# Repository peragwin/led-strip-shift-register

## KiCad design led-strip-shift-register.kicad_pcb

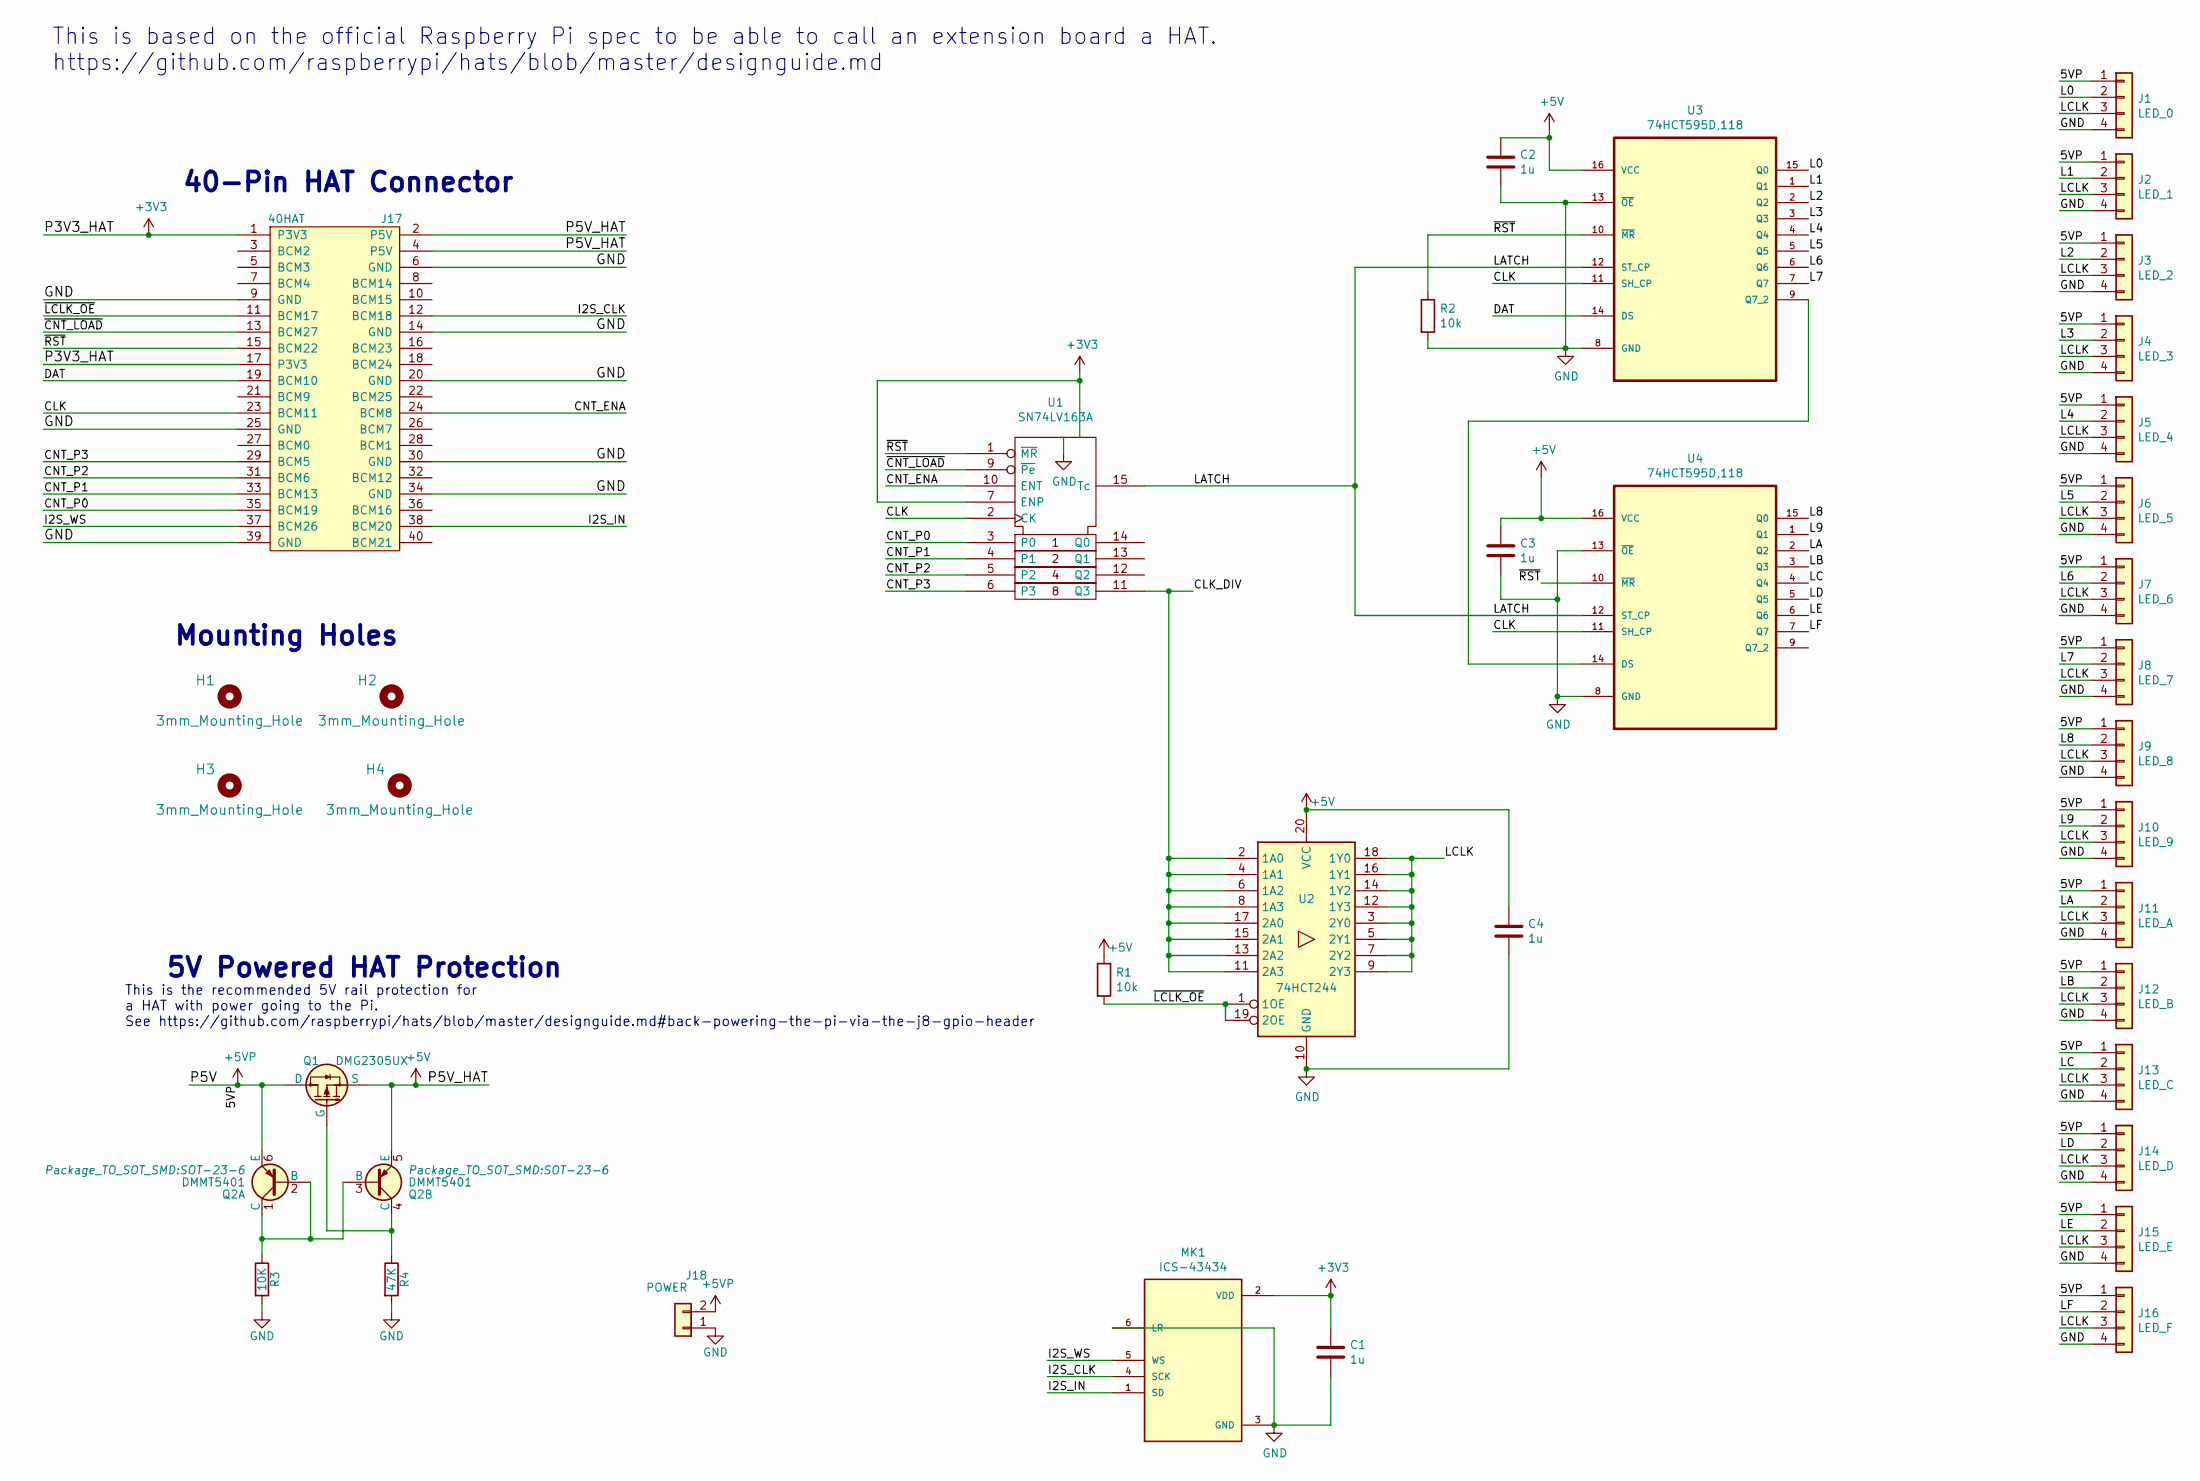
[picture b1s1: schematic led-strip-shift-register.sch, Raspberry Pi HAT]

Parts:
C1, C2, C3, C4: 1u; C_0603_1608Metric_Pad1.08x0.95mm_HandSolder
H1, H2, H3, H4: 3mm_Mounting_Hole; NPTH_3mm_ID
J1: LED_0; PinSocket_1x04_P2.54mm_Vertical
J2: LED_1; PinSocket_1x04_P2.54mm_Vertical
J3: LED_2; PinSocket_1x04_P2.54mm_Vertical
J4: LED_3; PinSocket_1x04_P2.54mm_Vertical
J5: LED_4; PinSocket_1x04_P2.54mm_Vertical
J6: LED_5; PinSocket_1x04_P2.54mm_Vertical
J7: LED_6; PinSocket_1x04_P2.54mm_Vertical
J8: LED_7; PinSocket_1x04_P2.54mm_Vertical
J9: LED_8; PinSocket_1x04_P2.54mm_Vertical
J10: LED_9; PinSocket_1x04_P2.54mm_Vertical
J11: LED_A; PinSocket_1x04_P2.54mm_Vertical
J12: LED_B; PinSocket_1x04_P2.54mm_Vertical
J13: LED_C; PinSocket_1x04_P2.54mm_Vertical
J14: LED_D; PinSocket_1x04_P2.54mm_Vertical
J15: LED_E; PinSocket_1x04_P2.54mm_Vertical
J16: LED_F; PinSocket_1x04_P2.54mm_Vertical
J17: 40HAT; PinSocket_2x20_P2.54mm_Vertical
J18: POWER; TerminalBlock_bornier-2_P5.08mm
MK1: ICS-43434; I2S-MIC_DIP-6
Q1: DMG2305UX; SOT-23
Q2: DMMT5401; SOT-23-6
R1, R2: 10k; R_0603_1608Metric_Pad0.98x0.95mm_HandSolder
R3: 10K; R_0603_1608Metric_Pad0.84x1.00mm_HandSolder
R4: 47K; R_0603_1608Metric_Pad0.84x1.00mm_HandSolder
U1: SN74LV163A; SOIC-16_3.9x9.9mm_P1.27mm
U2: 74HCT244; TSSOP-20_4.4x6.5mm_P0.65mm; LCSC C131088
U3, U4: 74HCT595D,118; SOIC127P600X175-16N; MPN 74HCT595D,118; LCSC C282339

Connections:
+3V3: C1.1, J17.1 (P3V3), J17.17 (P3V3), MK1.2 (VDD), U1.7 (ENP), U1.16 (VCC)
+5V: C2.1, C3.1, C4.1, J17.2 (P5V), J17.4 (P5V), Q1.2 (S), Q2.5 (E), R1.1, U2.20 (VCC), U3.16 (VCC), U4.16 (VCC)
+5VP: J1.1, J2.1, J3.1, J4.1, J5.1, J6.1, J7.1, J8.1, J9.1, J10.1, J11.1, J12.1, J13.1, J14.1, J15.1, J16.1, J18.2, Q1.3 (D), Q2.6 (E)
/CLK: J17.23 (BCM11), U1.2 (CK), U3.11 (SH_CP), U4.11 (SH_CP)
/CLK_DIV: U1.11 (Q3), U2.2 (1A0), U2.4 (1A1), U2.6 (1A2), U2.8 (1A3), U2.11 (2A3), U2.13 (2A2), U2.15 (2A1), U2.17 (2A0)
/CNT_ENA: J17.24 (BCM8), U1.10 (ENT)
/CNT_P0: J17.35 (BCM19), U1.3 (P0)
/CNT_P1: J17.33 (BCM13), U1.4 (P1)
/CNT_P2: J17.31 (BCM6), U1.5 (P2)
/CNT_P3: J17.29 (BCM5), U1.6 (P3)
/DAT: J17.19 (BCM10), U3.14 (DS)
/I2S_CLK: J17.12 (BCM18), MK1.4 (SCK)
/I2S_IN: J17.38 (BCM20), MK1.1 (SD)
/I2S_WS: J17.37 (BCM26), MK1.5 (WS)
/L0: J1.2, U3.15 (Q0)
/L1: J2.2, U3.1 (Q1)
/L2: J3.2, U3.2 (Q2)
/L3: J4.2, U3.3 (Q3)
/L4: J5.2, U3.4 (Q4)
/L5: J6.2, U3.5 (Q5)
/L6: J7.2, U3.6 (Q6)
/L7: J8.2, U3.7 (Q7)
/L8: J9.2, U4.15 (Q0)
/L9: J10.2, U4.1 (Q1)
/LA: J11.2, U4.2 (Q2)
/LATCH: U1.15 (Tc), U3.12 (ST_CP), U4.12 (ST_CP)
/LB: J12.2, U4.3 (Q3)
/LC: J13.2, U4.4 (Q4)
/LCLK: J1.3, J2.3, J3.3, J4.3, J5.3, J6.3, J7.3, J8.3, J9.3, J10.3, J11.3, J12.3, J13.3, J14.3, J15.3, J16.3, U2.3 (2Y0), U2.5 (2Y1), U2.7 (2Y2), U2.9 (2Y3), U2.12 (1Y3), U2.14 (1Y2), U2.16 (1Y1), U2.18 (1Y0)
/LD: J14.2, U4.5 (Q5)
/LE: J15.2, U4.6 (Q6)
/LF: J16.2, U4.7 (Q7)
/~CNT_LOAD: J17.13 (BCM27), U1.9 (~Pe)
/~LCLK_OE: J17.11 (BCM17), R1.2, U2.1 (1OE), U2.19 (2OE)
/~RST: J17.15 (BCM22), R2.1, U1.1 (~MR), U3.10 (~MR), U4.10 (~MR)
GND: C1.2, C2.2, C3.2, C4.2, J1.4, J2.4, J3.4, J4.4, J5.4, J6.4, J7.4, J8.4, J9.4, J10.4, J11.4, J12.4, J13.4, J14.4, J15.4, J16.4, J17.6 (GND), J17.9 (GND), J17.14 (GND), J17.20 (GND), J17.25 (GND), J17.30 (GND), J17.34 (GND), J17.39 (GND), J18.1, MK1.3 (GND), MK1.6 (LR), R2.2, R3.2, R4.2, U1.8 (GND), U2.10 (GND), U3.8 (GND), U3.13 (~OE), U4.8 (GND), U4.13 (~OE)
unnamed: Q1.1 (G), Q2.4 (C), R4.1
unnamed: Q2.1 (C), Q2.2 (B), Q2.3 (B), R3.1
unnamed: U3.9 (Q7_2), U4.14 (DS)

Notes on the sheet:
5V Powered HAT Protection
This is the recommended 5V rail protection for a HAT with power going to the Pi. See https://github.com/raspberrypi/hats/blob/master/designguide.md#back-powering-the-pi-via-the-j8-gpio-header
Mounting Holes
40-Pin HAT Connector
This is based on the official Raspberry Pi spec to be able to call an extension board a HAT. https://github.com/raspberrypi/hats/blob/master/designguide.md

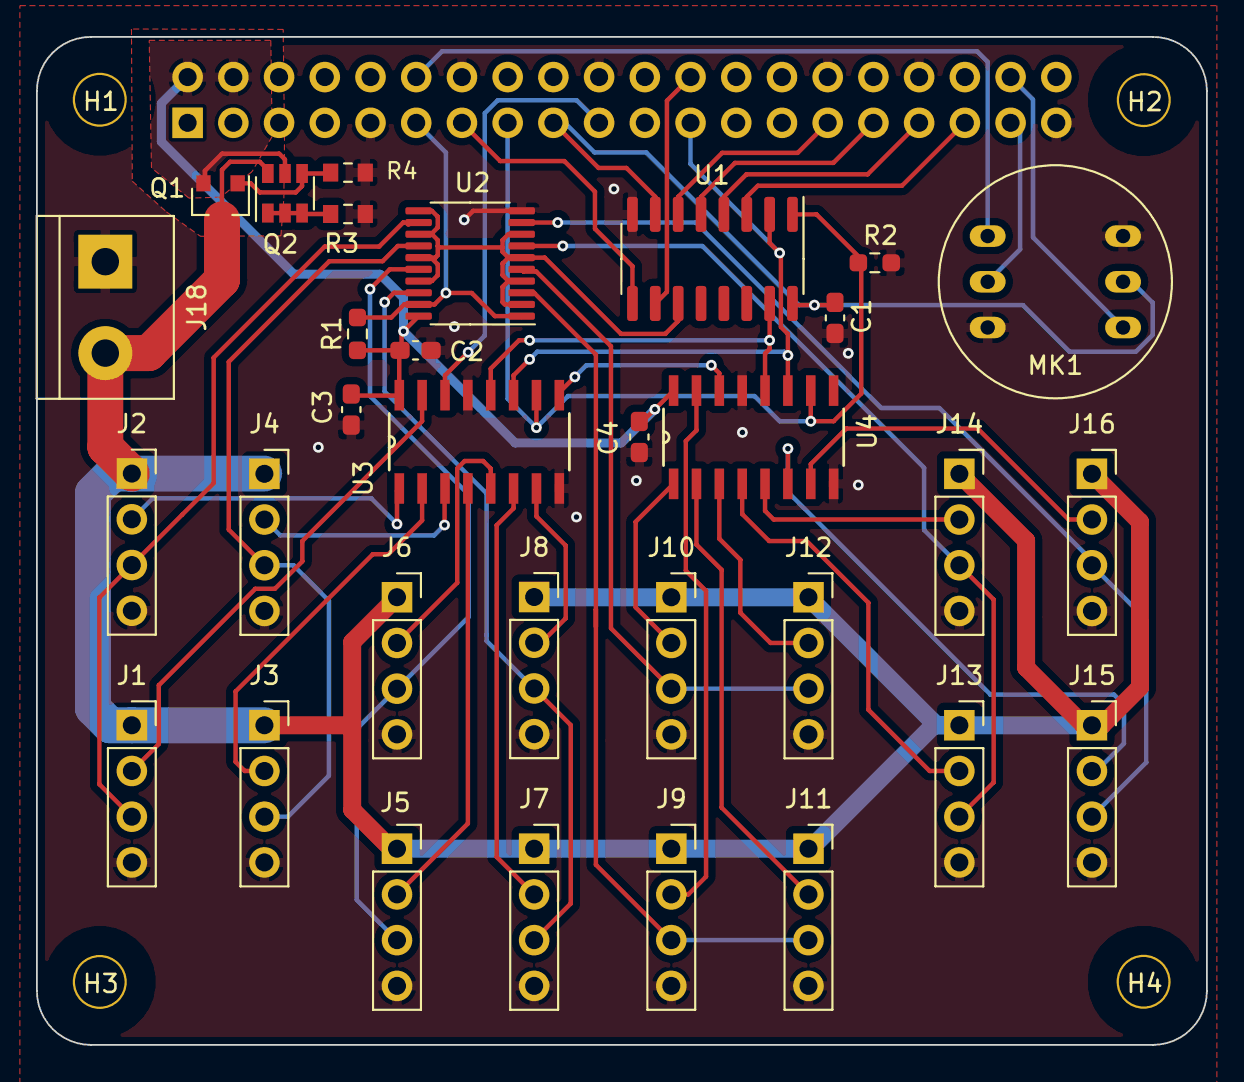
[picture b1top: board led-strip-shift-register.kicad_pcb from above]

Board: 2 copper layers, 65.0 x 56.0 mm, 37 parts (1 on the bottom side), 39 nets.

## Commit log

2021-02-07 initial commit with shift reg + counter
2021-02-07 mostly done hopefully
2021-02-07 revisions for components
2021-02-08 tweaks before submission
